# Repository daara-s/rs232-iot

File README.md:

# rs232-iot
RS-232 interface for wireless data acquisition of lab instruments using a Wemos D1 Mini microcontroller

## Goal
[Design an open source board with firmware compatible for data acquisition for a range of commonly used lab instruments](https://www.opencell.bio/summerprojects)

Initial prototyping cost: ~£10
- Wemos D1 Mini: ~£5
    - [Amazon reference](https://www.amazon.co.uk/AZDelivery-Development-ESP8266EX-Compatible-Micropython/dp/B08BTH77F3/ref=sr_1_3?dchild=1&keywords=wemos%2Bd1%2Bmini&qid=1623942509&sr=8-3&th=1)
- RS232 to TTL board: ~£5
    - [Amazon reference](https://www.amazon.co.uk/DollaTek-MAX3232-Serial-Converter-Connector/dp/B07DK3874B/ref=sr_1_3?dchild=1&keywords=rs232+to+ttl&qid=1623942563&sr=8-3)

### Roadmap
1. Research RS-232 baud rates and communication specifics of different lab instruments
2. Write a program in Arduino to confirm communication over all instrument RS-232 ports
4. Create main MQTT program to parse RS-232 data over WiFi
    * Using [EspMQTTClient](https://github.com/plapointe6/EspMQTTClient) library
5. Produce an RS-232 to TTL PCB shield for the Wemos D1 Mini using KiCAD
6. (optional) Design a 3D printed enclosure for the board in Fusion 360

### Other considerations
- Power: LiPo batteries vs USB vs wall socket
- integrating into existing [OpenCell fermentrack](https://github.com/tmopencell/sudo.bio) system

### RS-232 Shield
Shield board for the Wemos D1 Mini

### References
[Seeedstudio RS-232 to TTL converter](https://wiki.seeedstudio.com/RS-232_To_TTL_Conveter-MAX3232IDR/)
- licensed under: https://creativecommons.org/licenses/by/4.0/

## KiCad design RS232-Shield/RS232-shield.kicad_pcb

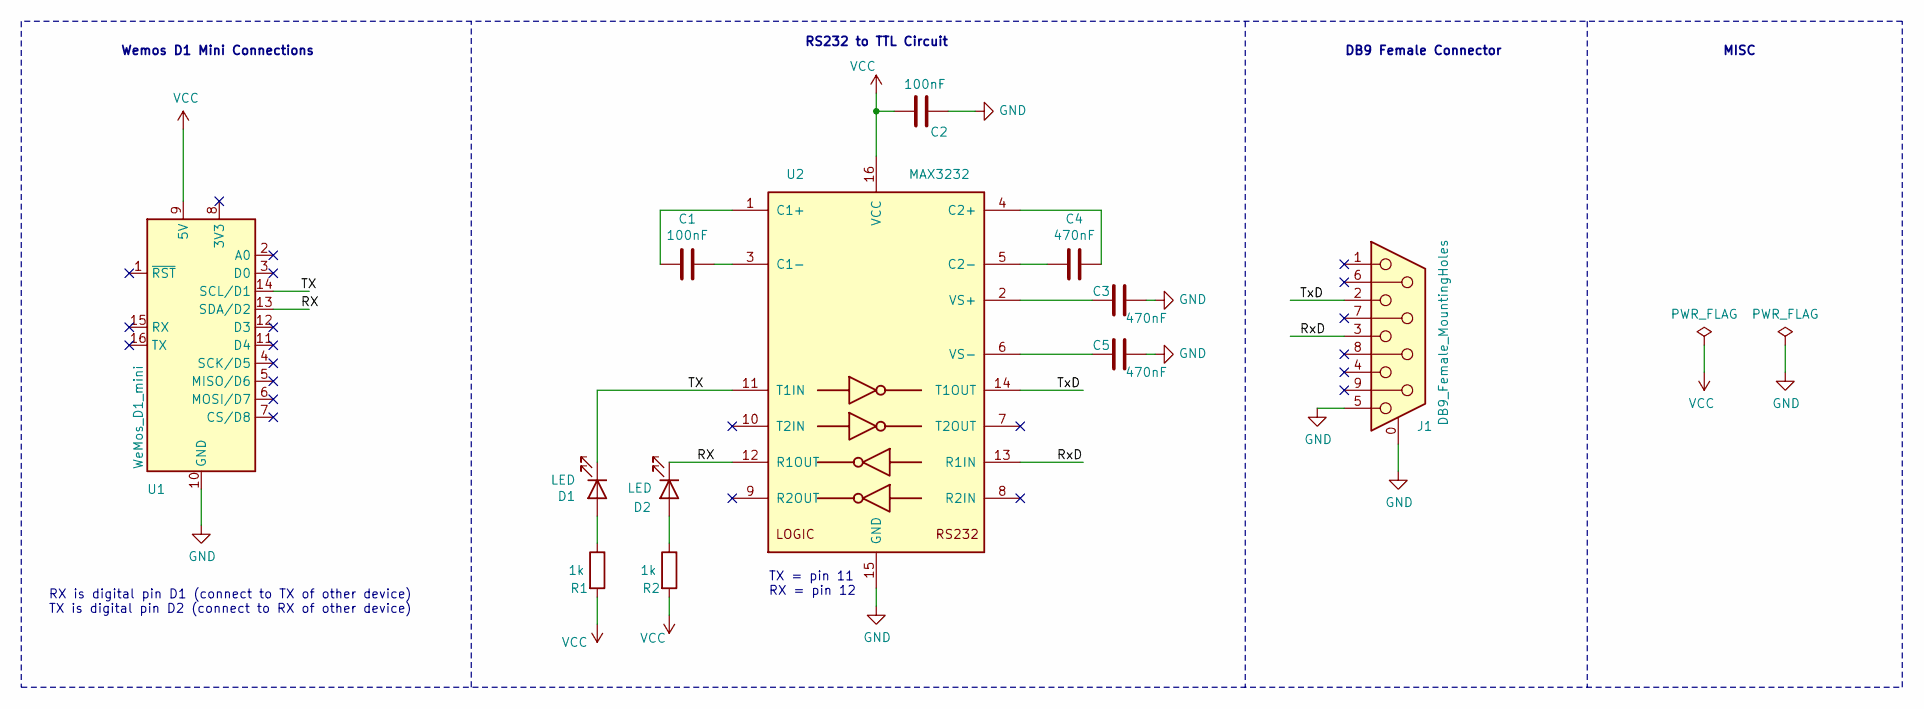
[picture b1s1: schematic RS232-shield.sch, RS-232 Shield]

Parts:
C1, C2: 100nF; C_0805_2012Metric_Pad1.18x1.45mm_HandSolder
C3, C4, C5: 470nF; C_0805_2012Metric_Pad1.18x1.45mm_HandSolder
D1, D2: LED; LED_0805_2012Metric_Pad1.15x1.40mm_HandSolder
J1: DB9_Female_MountingHoles; DSUB-9_Female_Horizontal_P2.77x2.84mm_EdgePinOffset4.94mm_H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
R1, R2: 1k; R_0805_2012Metric_Pad1.20x1.40mm_HandSolder
U1: WeMos_D1_mini; WEMOS_D1_mini_light
U2: MAX3232; SOIC-16_3.9x9.9mm_P1.27mm

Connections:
/RX: D2.1 (K), U1.13 (SDA/D2), U2.12 (R1OUT)
/RxD: J1.3, U2.13 (R1IN)
/TX: D1.1 (K), U1.14 (SCL/D1), U2.11 (T1IN)
/TxD: J1.2, U2.14 (T1OUT)
GND: C2.1, C3.1, C5.1, J1.0 (PAD), J1.5, U1.10 (GND), U2.15 (GND)
unnamed: C1.1, U2.3 (C1-)
unnamed: C1.2, U2.1 (C1+)
unnamed: C3.2, U2.2 (VS+)
unnamed: C4.1, U2.4 (C2+)
unnamed: C4.2, U2.5 (C2-)
unnamed: C5.2, U2.6 (VS-)
unnamed: D1.2 (A), R1.1
unnamed: D2.2 (A), R2.1
VCC: C2.2, R1.2, R2.2, U1.9 (5V), U2.16 (VCC)

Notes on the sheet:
TX = pin 11 RX = pin 12
RX is digital pin D1 (connect to TX of other device) TX is digital pin D2 (connect to RX of other device)
RS232 to TTL Circuit
Wemos D1 Mini Connections
DB9 Female Connector
MISC

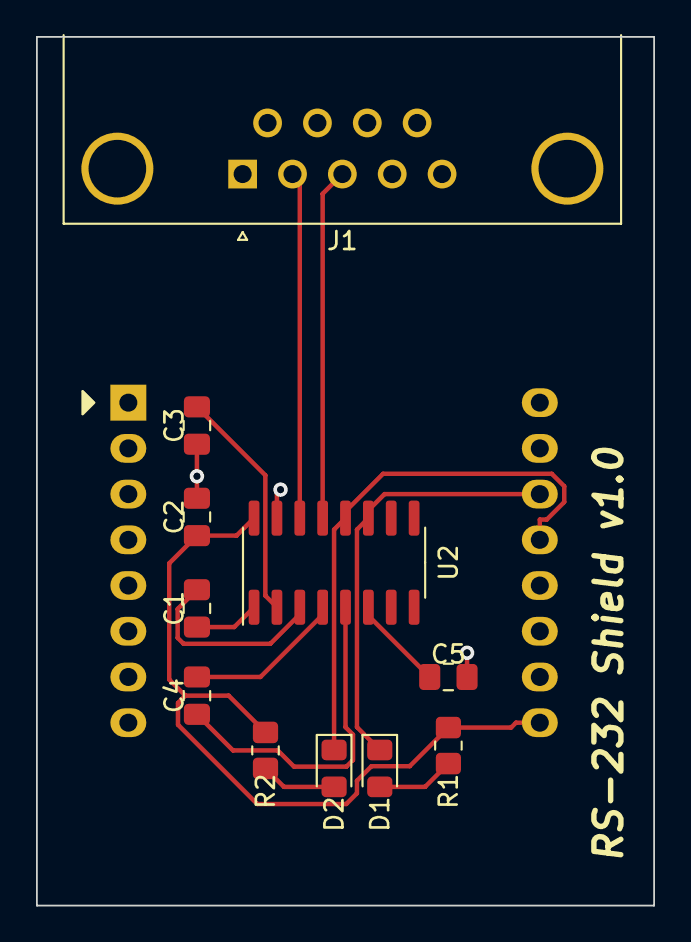
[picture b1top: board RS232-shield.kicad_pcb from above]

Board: 2 copper layers, 34.3 x 48.3 mm, 12 parts (0 on the bottom side), 14 nets.

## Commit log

2021-06-17 Add RS232 to TTL schematic and board layout
    Source: https://wiki.seeedstudio.com/RS-232_To_TTL_Conveter-MAX3232IDR/
2021-06-17 Rename RS232 to TTL Converter (MAX3232IDR).brd to rs232/RS232 to TTL Converter (MAX3232IDR).brd
2021-06-17 Rename RS232 to TTL Converter (MAX3232IDR).sch to rs232/RS232 to TTL Converter (MAX3232IDR).sch
2021-06-17 Add consideration of existing fermentrack system
    Also add goal link
2021-06-18 Add RS-232 serial passthrough program
    Allows parsing data directly to the serial monitor, allowing for debugging and building MQTT program
2021-06-18 Change MQTT libary
2021-06-18 Add MQTT client template
    Program to be modified after testing with RS-232 passthrough
2021-06-18 Add references section
    Moved schematic to references section
2021-06-19 Add RS-232 Shield Schematic
    Schematic for an RS-232 shield to mount on a Wemos D1 Mini board via headers
2021-06-19 Reorganise folder structure, add shield schematic image
2021-06-20 Add RS-232 Shield PCB layout
2021-07-06 Modify PCB silkscreens
    Project-specific footprint added for Wemos D1 Mini
2021-07-06 Add board name to silkscreen

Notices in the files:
RS232-Shield/RS232-shield.sch:
CC BY-SA 4.0
